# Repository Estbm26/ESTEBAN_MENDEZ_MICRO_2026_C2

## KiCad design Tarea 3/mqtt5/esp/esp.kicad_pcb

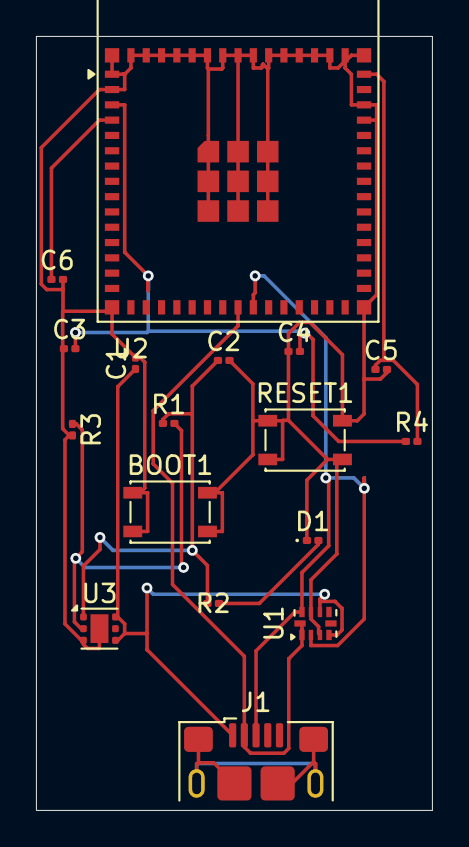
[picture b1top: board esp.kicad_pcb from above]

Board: 2 copper layers, 22.0 x 43.0 mm, 17 parts (0 on the bottom side), 10 nets.

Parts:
BOOT1: SW_MEC_5E; SW_SPST_PTS810
C1, C2, C3: 10uF; C_0201_0603Metric
C4, C5, C6: 0.1uF; C_0201_0603Metric
D1: LED; LED_0201_0603Metric
J1: USB_B_Micro; USB_Micro-B_Amphenol_10118193-0001LF_Horizontal
R1: 1M; R_0201_0603Metric
R2: 5.1K; R_0201_0603Metric
R3: 200K; R_0201_0603Metric
R4: 10K; R_0201_0603Metric
RESET1: SW_MEC_5E; SW_SPST_PTS810
U1: D3V3XA4B10LP; Texas_R-PUQFN-N10
U2: ESP32-S3-MINI-1U; ESP32-S2-MINI-1
U3: TLV75801PDRV; WSON-6-1EP_2x2mm_P0.65mm_EP1x1.6mm

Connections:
5VUSB: C1.1, J1.1 (VBUS), U1.4, U1.7 (NC), U3.4 (EN), U3.6 (IN)
/3V3: C3.2, C4.2, R4.1, U2.3 (3V3)
/ESP32_EN: C5.1, R4.2, U2.45 (EN)
/GPIDO: C6.1, U2.4 (IO0)
/USB_N: J1.2 (D-), U1.1, U1.10 (NC), U2.23 (USB_D-)
/USB_P: J1.3 (D+), U1.2, U1.9 (NC), U2.24 (USB_D+)
GND: BOOT1.1, BOOT1.2, C1.2, C2.2, C3.1, C4.1, C5.2, C6.2, D1.1 (K), R3.2, RESET1.1, RESET1.2, U1.3 (VSS), U1.8 (VSS), U2.1 (GND), U2.2 (GND), U2.42 (GND), U2.43 (GND), U2.46 (GND), U2.47 (GND), U2.48 (GND), U2.49 (GND), U2.50 (GND), U2.51 (GND), U2.52 (GND), U2.53 (GND), U2.54 (GND), U2.55 (GND), U2.56 (GND), U2.57 (GND), U2.58 (GND), U2.59 (GND), U2.60 (GND), U2.61 (GND), U2.62 (GND), U2.63 (GND), U2.64 (GND), U2.65 (GND), U3.3 (GND), U3.7 (GND)
unnamed: D1.2 (A), R2.2
unnamed: R1.2, R3.1, U3.2 (FB)
unnamed: C2.1, R1.1, R2.1, U3.1 (OUT)

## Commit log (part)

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2026-06-11 Esp1
